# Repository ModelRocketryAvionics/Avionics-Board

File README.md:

# ModelRocketAvionicsPCB
'Cheap', Easy Avionics for Model Rockets!

Howdy! This is a repo for an avionics board designed for small scale model rockets. The goal of the project is to provide an easy to integrate system that provides telemetry data measurements. 

The main features are:
- 3 DOF Accelerometer (upto 24g)
- 3 DOF Gyroscope
- Barometric Pressure/Altitude sensor
- microSD Card data storage
- USB for charging, reprogramming and microSD card reading*
- Expansion header for future functionality called "Stages" (see below)

*Usb programming and microSD card reading probably won't be implemented initially.

Potential/Planned Stages/Expansion Boards:
- Radio link/communications (Provides real-time telemetry data over a short range wireless link)
- Relay/Switcher (Provides high-power switching for ignition of additional charges/engines, deploy parachutes, etc)
- Additional Sensors Expansions (Additional Sensors like GPS, etc)

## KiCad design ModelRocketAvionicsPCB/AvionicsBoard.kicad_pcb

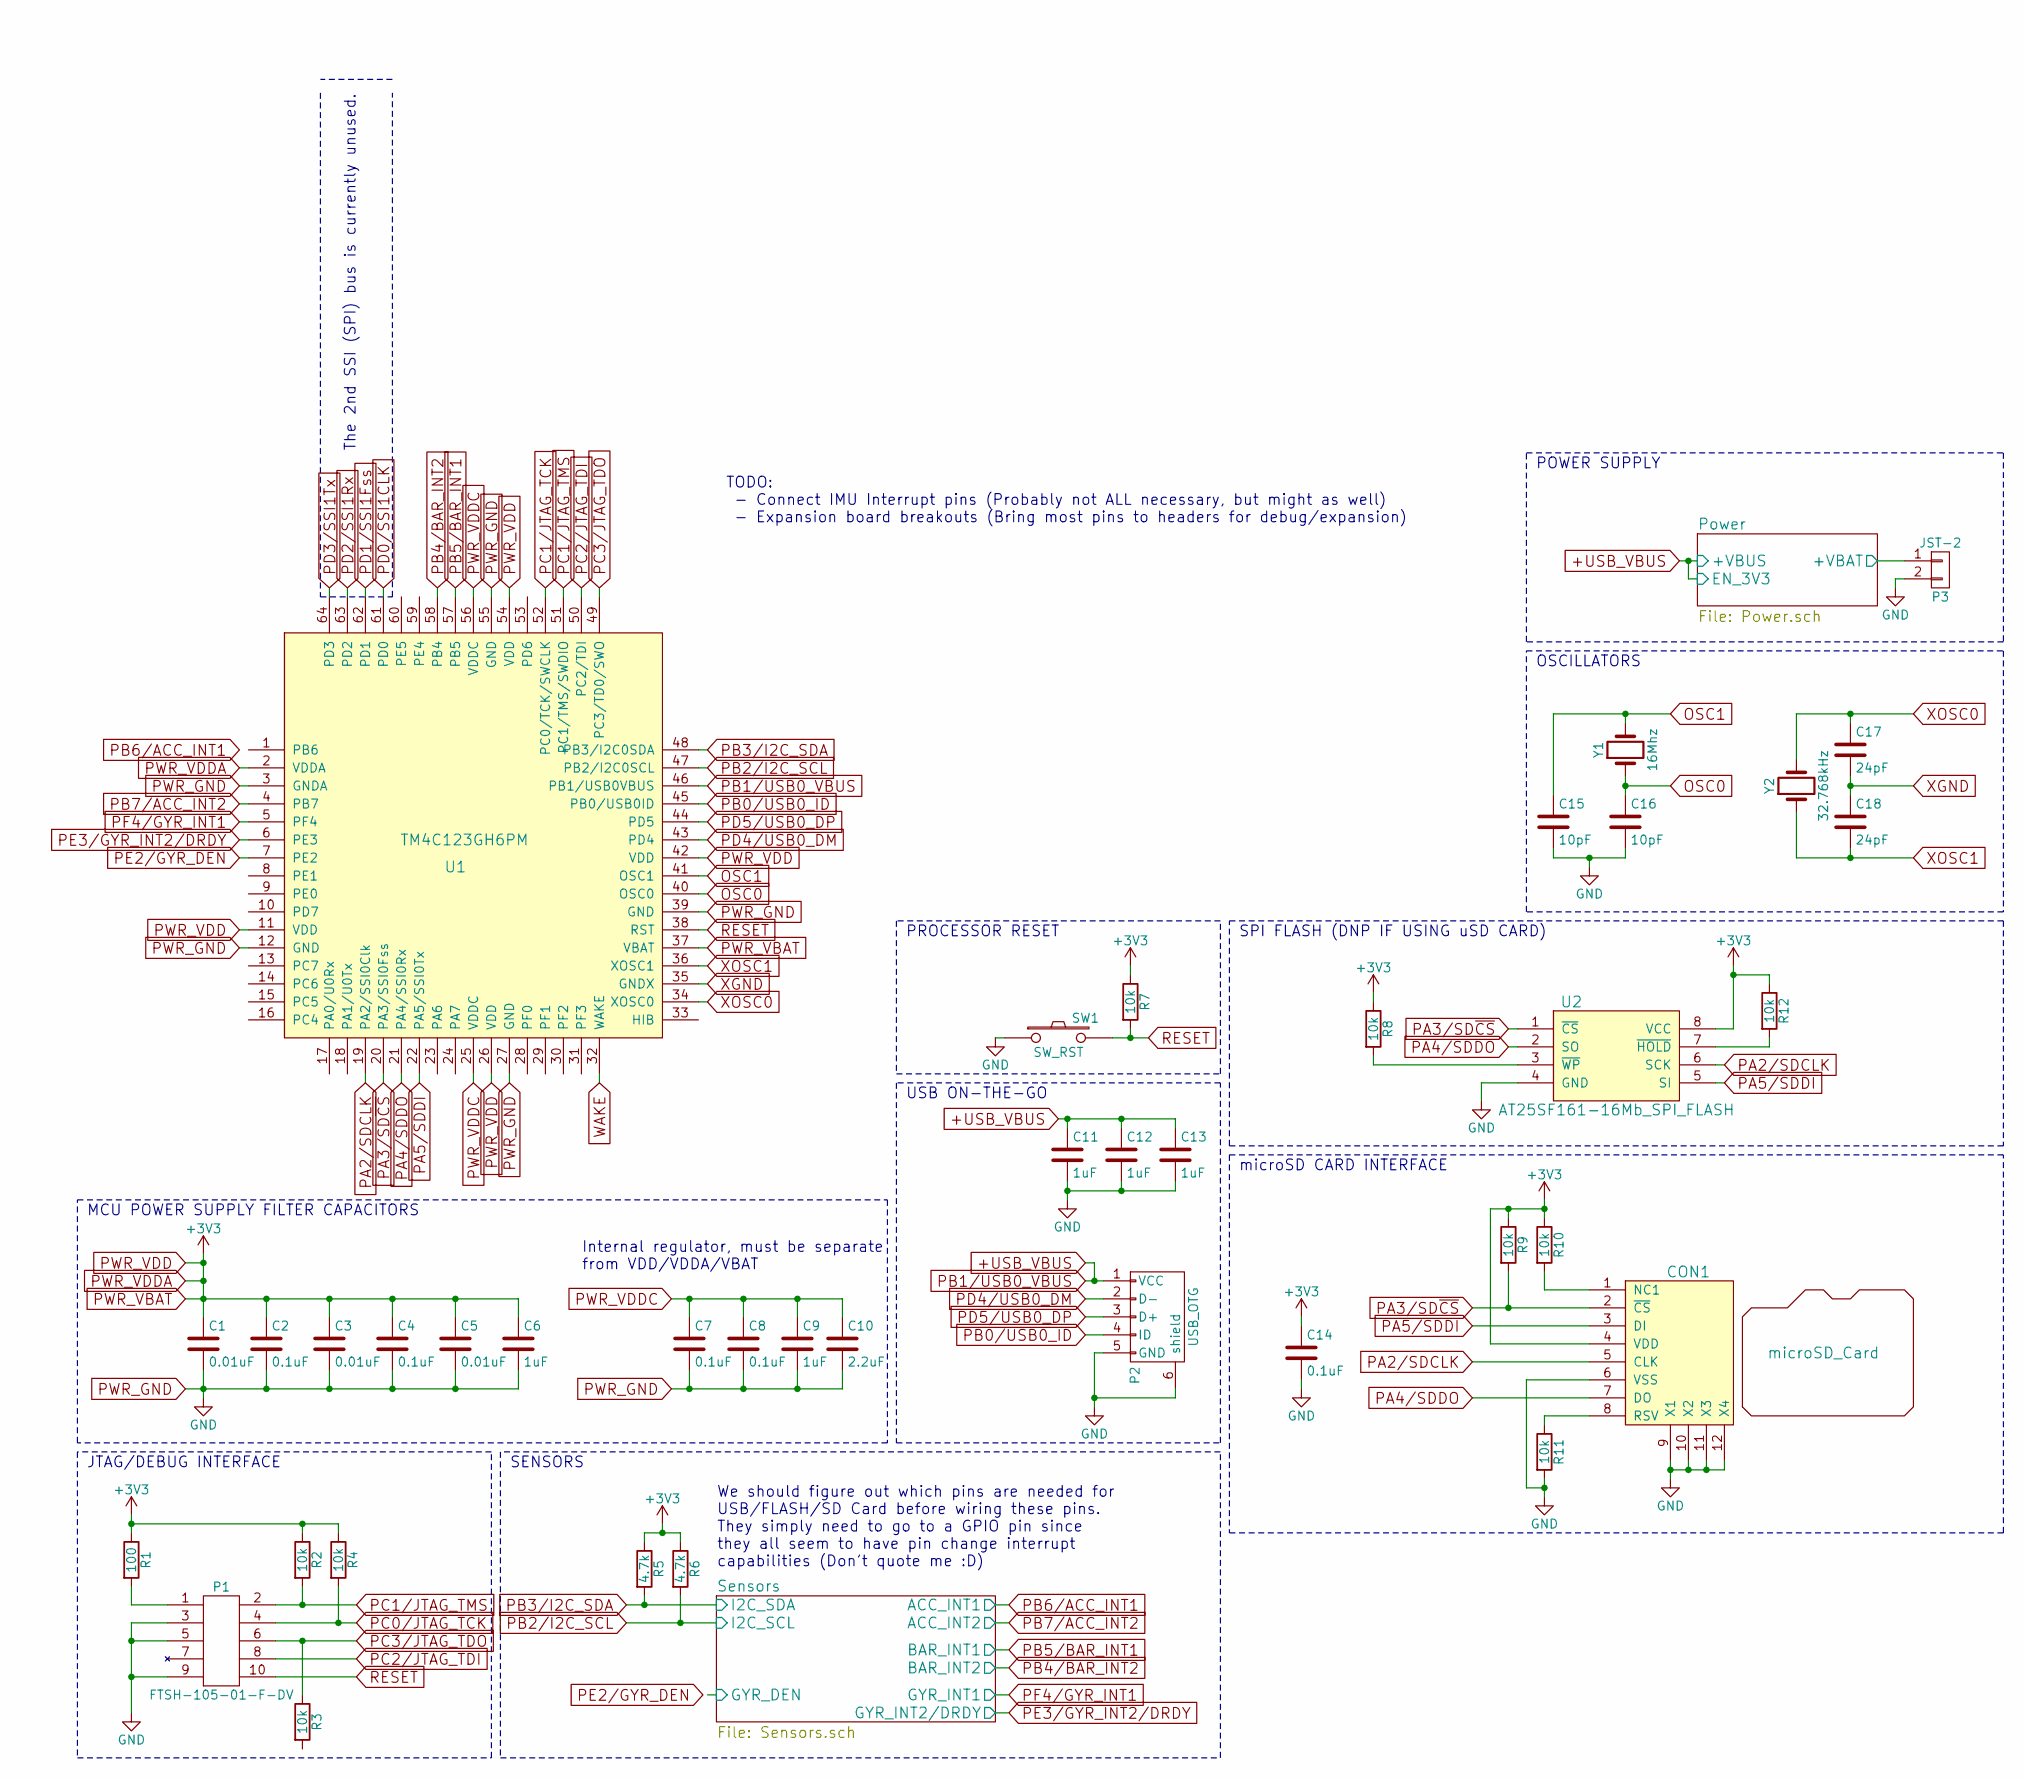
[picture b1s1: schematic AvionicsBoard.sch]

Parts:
C1, C3, C5: 0.01uF; C_0402; Digi-Key Part Number 478-7867-1-ND
C2, C4, C7, C8, C14: 0.1uF; C_0402; Digi-Key Part Number 587-4552-1-ND
C6, C9, C11, C12, C13: 1uF; C_0603; Digi-Key Part Number 490-1543-1-ND
C10: 2.2uF; C_0603; Digi-Key Part Number 490-3296-1-ND
C15, C16: 10pF; C_0402; Digi-Key Part Number 712-1252-1-ND
C17: 24pF; C_0402; Digi-Key Part Number 478-10149-1-ND
C18: 24pF; C_0402
CON1: microSD_Card; Micro_SD_WM11190CT; Digi-Key Part Number WM11190CT-ND
P1: FTSH-105-01-F-DV; FTSH-105-01-F-DV-K; Digi-Key Part Number SAM8796-ND
P2: USB_OTG; USB_Connector_ZX62-B-5PA; Digi-Key Part Number H125279CT-ND
P3: JST-2; JST_B2B-EH-A(LF)(SN); Digi-Key Part Number 455-1611-ND
R1: 100; R_0402; Digi-Key Part Number P100DECT-ND
R2, R3, R4, R7, R8, R9, R10, R11, R12: 10k; R_0402; Digi-Key Part Number 311-10.0KLRCT-ND
R5, R6: 4.7k; R_0402; Digi-Key Part Number P4.7KDCCT-ND
SW1: SW_RST; Push_Button_B3S-1000; Digi-Key Part Number SW415-ND
U1: TM4C123GH6PM; TM4C123GH6PMI; Digi-Key Part Number 296-46360-1-ND
U2: AT25SF161-16Mb_SPI_FLASH; Flash_Mem_AT25SF161-SSHD; Digi-Key Part Number 1265-1230-1-ND
Y1: 16Mhz; 16MHz_Clock; Manufacturer Part No NX5032GA-16.000000MHZ-LN-CD-1; Digi-Key Part Number 631-1150-1-ND
Y2: 32.768kHz; Crystal_32768Hz_Radial_Can; Digi-Key Part Number 535-9034-ND

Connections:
+USB_VBUS: C11.1, C12.1, C13.1, P2.1 (VCC), U1.46 (PB1/USB0VBUS); also elsewhere on the board
+VBAT: P3.1; also elsewhere on the board
ACC_CS: C1.1, C2.1, C3.1, C4.1, C5.1, C6.1, C14.1, CON1.4 (VDD), R1.1, R2.1, R4.1, R5.1, R6.1, R7.1, R8.1, R9.1, R10.1, R12.1, U1.2 (VDDA), U1.11 (VDD), U1.26 (VDD), U1.37 (VBAT), U1.42 (VDD), U1.54 (VDD), U2.8 (VCC); also elsewhere on the board
HIB: U1.33 (HIB); also elsewhere on the board
unnamed 10: CON1.1 (NC1), R10.2; also elsewhere on the board
unnamed 11: CON1.8 (RSV), R11.1; also elsewhere on the board
unnamed: P1.1 (3V3), R1.2
unnamed: R8.2, U2.3 (~WP)
unnamed: R12.2, U2.7 (~HOLD)
OSC0: C16.1, U1.40 (OSC0), Y1.1
OSC1: C15.1, U1.41 (OSC1), Y1.2
PA0/U0Rx: U1.17 (PA0/U0Rx); also elsewhere on the board
PA1/U0Tx: U1.18 (PA1/U0Tx); also elsewhere on the board
PA2/SDCLK: CON1.5 (CLK), U1.19 (PA2/SSI0Clk), U2.6 (SCK); also elsewhere on the board
PA3/SD~CS: CON1.2 (~CS), R9.2, U1.20 (PA3/SSI0Fss), U2.1 (~CS); also elsewhere on the board
PA4/SDDO: CON1.7 (DO), U1.21 (PA4/SSI0Rx), U2.2 (SO); also elsewhere on the board
PA5/SDDI: CON1.3 (DI), U1.22 (PA5/SSI0Tx), U2.5 (SI); also elsewhere on the board
PA6: U1.23 (PA6); also elsewhere on the board
PA7: U1.24 (PA7); also elsewhere on the board
PB0/USB0_ID: P2.4 (ID), U1.45 (PB0/USB0ID)
PB2/I2C_SCL: R6.2, U1.47 (PB2/I2C0SCL); also elsewhere on the board
PB3/I2C_SDA: R5.2, U1.48 (PB3/I2C0SDA); also elsewhere on the board
PB4: U1.58 (PB4); also elsewhere on the board
PB5: U1.57 (PB5); also elsewhere on the board
PB6/GYR_INT2/DRDY: U1.1 (PB6); also elsewhere on the board
PB7/GYR_INT1: U1.4 (PB7); also elsewhere on the board
PC1/JTAG_TMS: P1.2 (JTAG_TMS), R2.2, U1.51 (PC1/TMS/SWDIO)
PC2/JTAG_TDI: P1.8 (JTAG_TDO), U1.50 (PC2/TDI)
PC3/JTAG_TDO: P1.6 (JTAG_TDO), R3.1, U1.49 (PC3/TD0/SWO)
PC4: U1.16 (PC4); also elsewhere on the board
PC5: U1.15 (PC5); also elsewhere on the board
PC6: U1.14 (PC6); also elsewhere on the board
PC7: U1.13 (PC7); also elsewhere on the board
PD0/SSI1CLK: U1.61 (PD0); also elsewhere on the board
PD1/SSI1Fss: U1.62 (PD1); also elsewhere on the board
PD2/SSI1Rx: U1.63 (PD2); also elsewhere on the board
PD3/SSI1Tx: U1.64 (PD3); also elsewhere on the board
PD6: U1.53 (PD6); also elsewhere on the board
PD7: U1.10 (PD7); also elsewhere on the board
PE0: U1.9 (PE0); also elsewhere on the board
PE1/IND_LED: U1.8 (PE1); also elsewhere on the board
PE2/ACC_INT2: U1.7 (PE2); also elsewhere on the board
PE3/ACC_INT1: U1.6 (PE3); also elsewhere on the board
PE4: U1.59 (PE4); also elsewhere on the board
PE5: U1.60 (PE5); also elsewhere on the board
PF0: U1.28 (PF0)
PF1: U1.29 (PF1)
PF2/BAR_INT1: U1.30 (PF2); also elsewhere on the board
PF3/BAR_INT2: U1.31 (PF3); also elsewhere on the board
PF4/GYR_DEN: U1.5 (PF4); also elsewhere on the board
PWR_GND: C1.2, C2.2, C3.2, C4.2, C5.2, C6.2, C7.2, C8.2, C9.2, C10.2, C11.2, C12.2, C13.2, C14.2, C15.2, C16.2, CON1.6 (VSS), CON1.9 (X1), CON1.10 (X2), CON1.11 (X3), CON1.12 (X4), P1.3 (GND), P1.5 (GND), P1.9 (GND), P2.5 (GND), P2.6 (shield), P3.2, R3.2, R11.2, SW1.1, U1.3 (GNDA), U1.12 (GND), U1.27 (GND), U1.39 (GND), U1.55 (GND), U2.4 (GND); also elsewhere on the board
PWR_VDDC: C7.1, C8.1, C9.1, C10.1, U1.25 (VDDC), U1.56 (VDDC)
RESET: P1.10 (RST_N), R7.2, SW1.2, U1.38 (RST); also elsewhere on the board
USB0_D+: P2.3 (D+), U1.44 (PD5)
USB0_D-: P2.2 (D-), U1.43 (PD4)
WAKE: U1.32 (WAKE); also elsewhere on the board
XGND: C17.2, C18.1, U1.35 (GNDX)
XOSC0: C17.1, U1.34 (XOSC0), Y2.2
XOSC1: C18.2, U1.36 (XOSC1), Y2.1

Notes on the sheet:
We should figure out which pins are needed for USB/FLASH/SD Card before wiring these pins. They simply need to go to a GPIO pin since they all seem to have pin change interrupt capabilities (Don't quote me :D)
JTAG/DEBUG INTERFACE
SENSORS
MCU POWER SUPPLY FILTER CAPACITORS
Internal regulator, must be separate from VDD/VDDA/VBAT
microSD CARD INTERFACE
SPI FLASH (DNP IF USING uSD CARD)
USB ON-THE-GO
TODO: - Connect IMU Interrupt pins (Probably not ALL necessary, but might as well) - Expansion board breakouts (Bring most pins to headers for debug/expansion)
The 2nd SSI (SPI) bus is currently unused.
OSCILLATORS
PROCESSOR RESET
POWER SUPPLY

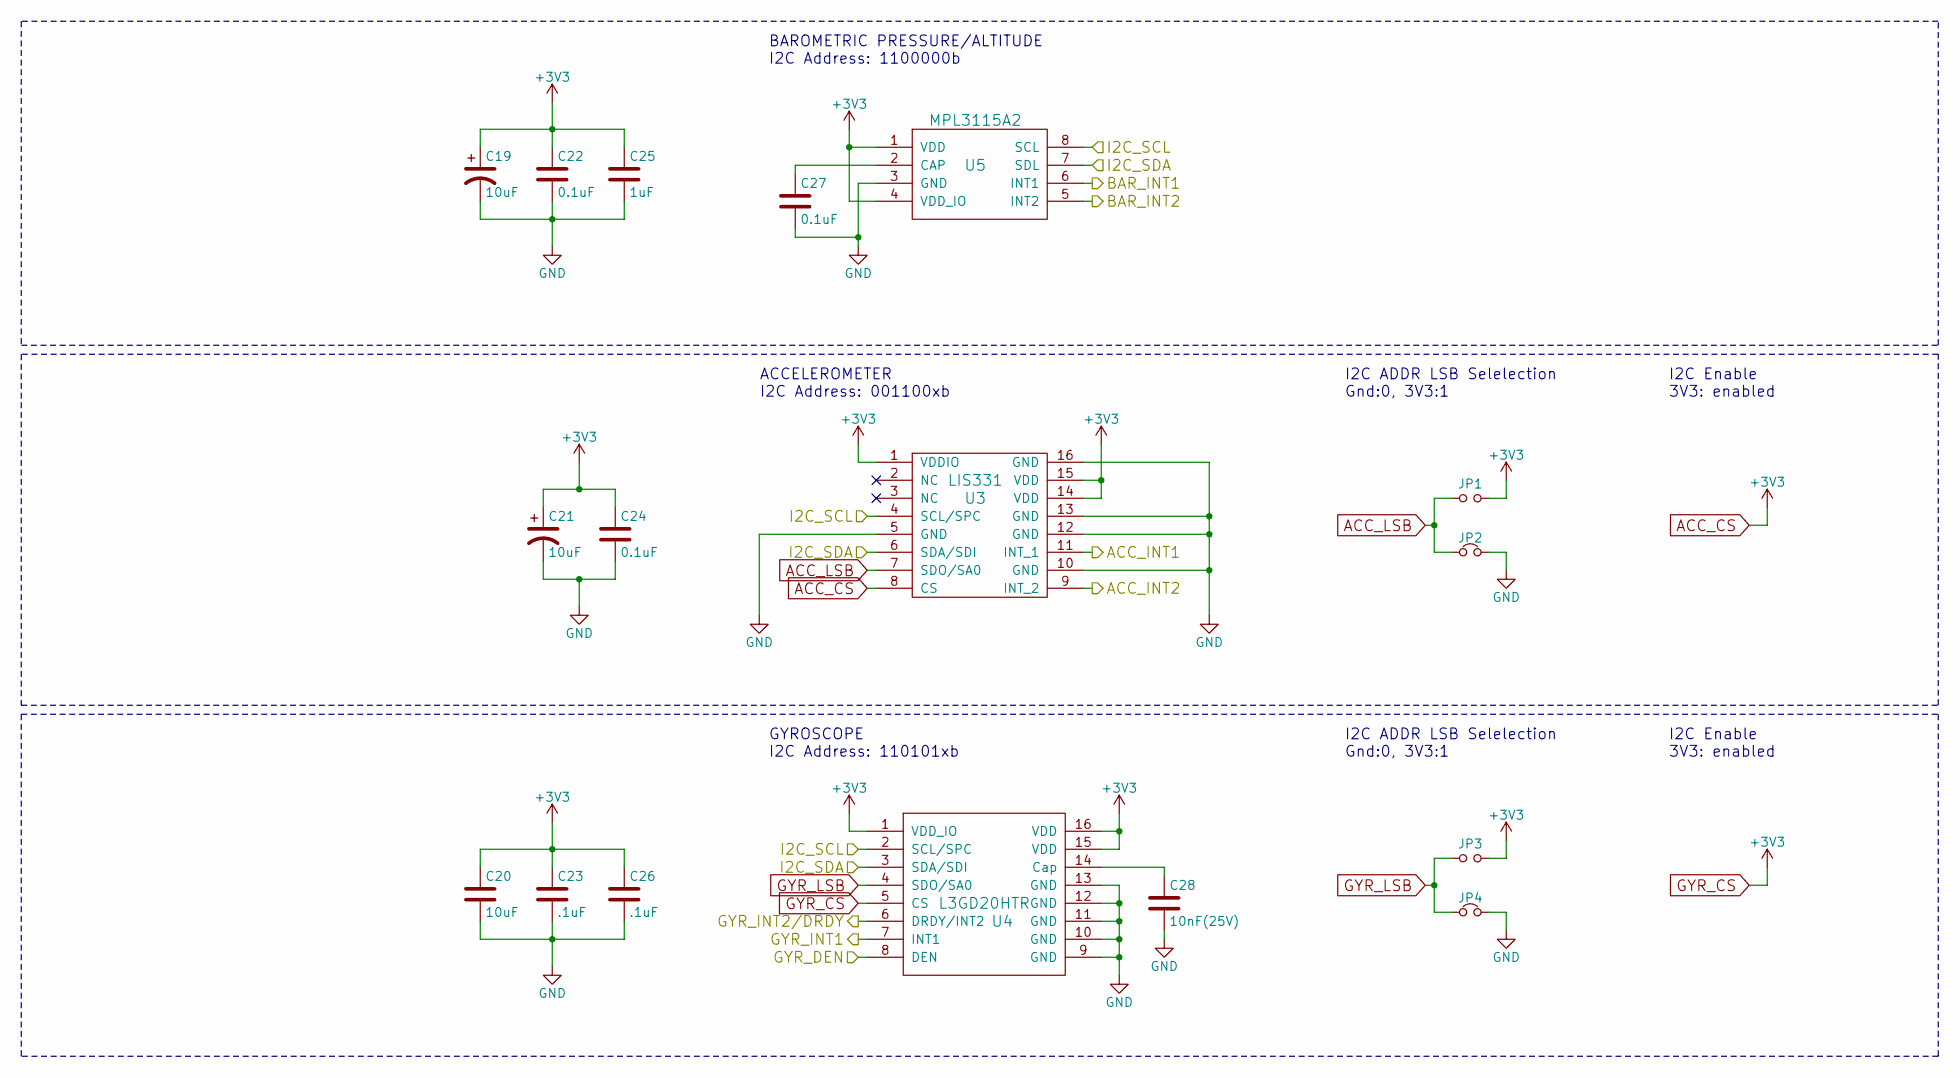
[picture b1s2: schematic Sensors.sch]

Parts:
C19, C21: 10uF; C_1206; Digi-Key Part Number 478-10756-1-ND
C20: 10uF; C_0603; Digi-Key Part Number 1276-1871-1-ND
C22, C24, C27: 0.1uF; C_0402; Digi-Key Part Number 587-4552-1-ND
C23, C26: .1uF; C_0402; Digi-Key Part Number 587-4552-1-ND
C25: 1uF; C_0603; Digi-Key Part Number 490-1543-1-ND
C28: 10nF(25V); C_0402; Digi-Key Part Number 478-7867-1-ND
JP1, JP3: Jumper_NO_Small; NO_Jumper
JP2, JP4: Jumper_NC_Small; NC_Jumper
U3: LIS331; LIS331HH; Digi-Key Part Number 497-10134-ND
U4: L3GD20HTR; Gyro_L3GD20HTR; Digi-Key Part Number 497-13931-1-ND
U5: MPL3115A2; Digi-Key Part Number MPL3115A2-ND

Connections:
ACC_CS: C19.1, C20.1, C21.1, C22.1, C23.1, C24.1, C25.1, C26.1, JP1.2, JP3.2, U3.1 (VDDIO), U3.8 (CS), U3.14 (VDD), U3.15 (VDD), U4.1 (VDD_IO), U4.5 (CS), U4.15 (VDD), U4.16 (VDD), U5.1 (VDD), U5.4 (VDD_IO); also elsewhere on the board
ACC_LSB: JP1.1, JP2.1, U3.7 (SDO/SA0)
GYR_LSB: JP3.1, JP4.1, U4.4 (SDO/SA0)
unnamed: C27.1, U5.2 (CAP)
unnamed: C28.1, U4.14 (Cap)
PB2/I2C_SCL: U3.4 (SCL/SPC), U4.2 (SCL/SPC), U5.8 (SCL); also elsewhere on the board
PB3/I2C_SDA: U3.6 (SDA/SDI), U4.3 (SDA/SDI), U5.7 (SDL); also elsewhere on the board
PB6/GYR_INT2/DRDY: U4.6 (DRDY/INT2); also elsewhere on the board
PB7/GYR_INT1: U4.7 (INT1); also elsewhere on the board
PE2/ACC_INT2: U3.9 (INT_2); also elsewhere on the board
PE3/ACC_INT1: U3.11 (INT_1); also elsewhere on the board
PF2/BAR_INT1: U5.6 (INT1); also elsewhere on the board
PF3/BAR_INT2: U5.5 (INT2); also elsewhere on the board
PF4/GYR_DEN: U4.8 (DEN); also elsewhere on the board
PWR_GND: C19.2, C20.2, C21.2, C22.2, C23.2, C24.2, C25.2, C26.2, C27.2, C28.2, JP2.2, JP4.2, U3.5 (GND), U3.10 (GND), U3.12 (GND), U3.13 (GND), U3.16 (GND), U4.9 (GND), U4.10 (GND), U4.11 (GND), U4.12 (GND), U4.13 (GND), U5.3 (GND); also elsewhere on the board

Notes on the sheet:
I2C ADDR LSB Selelection Gnd:0, 3V3:1
I2C Enable 3V3: enabled
ACCELEROMETER I2C Address: 001100xb
BAROMETRIC PRESSURE/ALTITUDE I2C Address: 1100000b
GYROSCOPE I2C Address: 110101xb

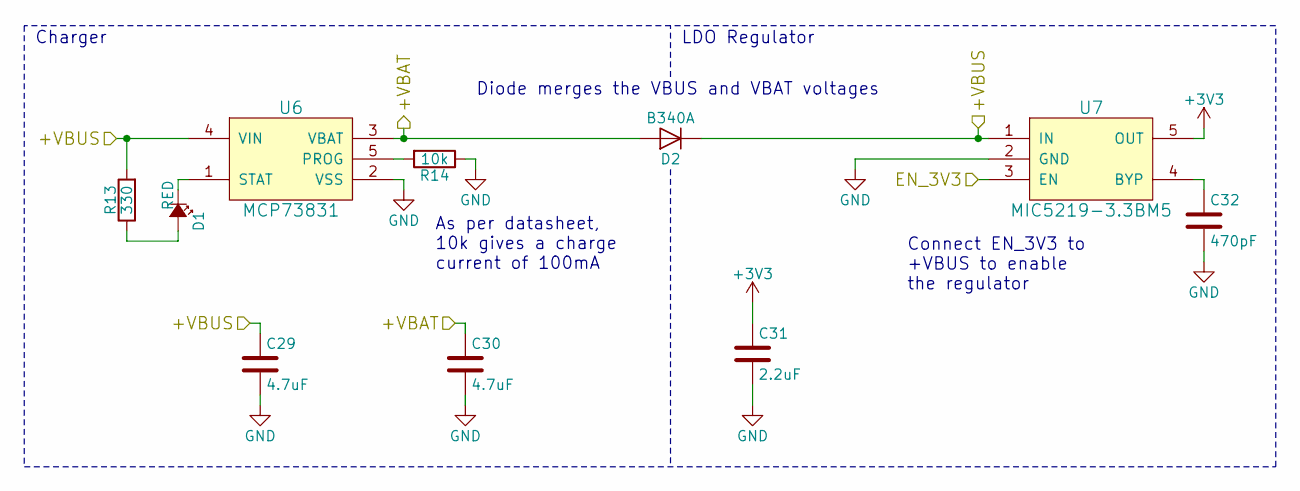
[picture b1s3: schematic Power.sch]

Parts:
C29, C30: 4.7uF; C_0603; Rated Voltage 16V; Digi-Key Part Number 445-7478-1-ND
C31: 2.2uF; C_0603; Digi-Key Part Number 490-3296-1-ND
C32: 470pF; C_0402; Digi-Key Part Number 490-1300-1-ND
D1: RED; R_0603; Digi-Key Part Number 160-1447-1-ND
D2: B340A; Digi-Key Part Number B340A-FDICT-ND
R13: 330; R_0402; Digi-Key Part Number RR05P330DCT-ND
R14: 10k; R_0402; Digi-Key Part Number 311-10.0KLRCT-ND
U6: MCP73831; MCP73831T-2ACI&slash_OT; Digi-Key Part Number MCP73831T-2ACI/OTCT-ND
U7: MIC5219-3.3BM5; MIC5219-3.3YM5-TR; Digi-Key Part Number 576-1281-1-ND

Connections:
+USB_VBUS: C29.1, D2.1 (K), R13.2, U6.4 (VIN), U7.1 (IN), U7.3 (EN); also elsewhere on the board
+VBAT_ON: C30.1, D2.2 (A), U6.3 (VBAT); also elsewhere on the board
ACC_CS: C31.1, U7.5 (OUT); also elsewhere on the board
unnamed: C32.1, U7.4 (BYP)
unnamed: D1.1 (K), U6.1 (STAT)
unnamed: D1.2 (A), R13.1
unnamed: R14.2, U6.5 (PROG)
PWR_GND: C29.2, C30.2, C31.2, C32.2, R14.1, U6.2 (VSS), U7.2 (GND); also elsewhere on the board

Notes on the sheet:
Diode merges the VBUS and VBAT voltages
Charger
LDO Regulator
As per datasheet, 10k gives a charge current of 100mA
Connect EN_3V3 to +VBUS to enable the regulator

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
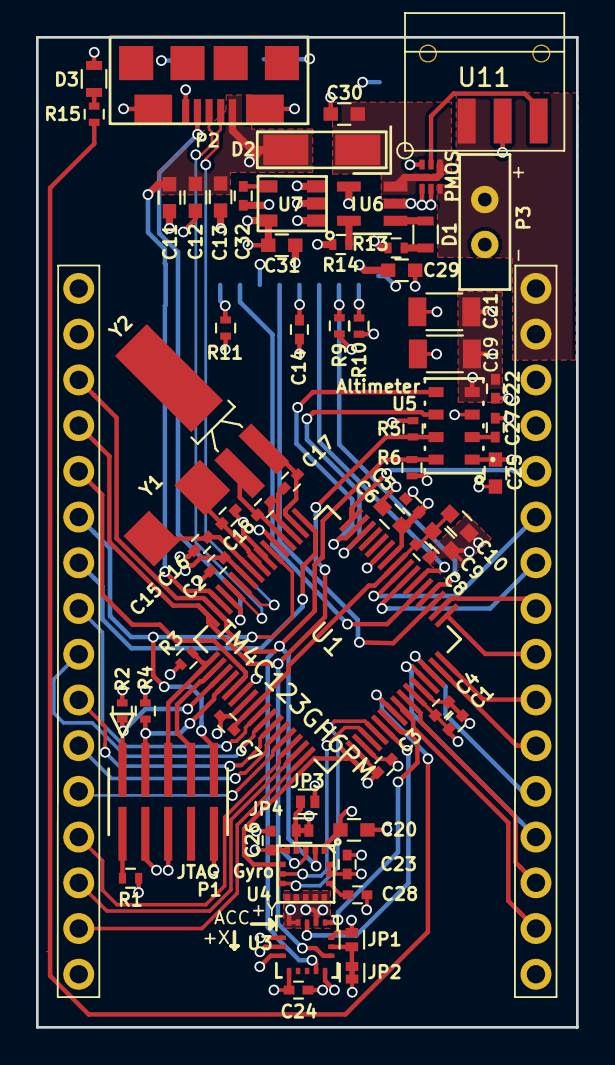
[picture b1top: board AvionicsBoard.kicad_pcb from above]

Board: 4 copper layers, 30.0 x 55.0 mm, 67 parts (1 on the bottom side), 67 nets.

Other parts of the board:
D3: Led_Small; R_0603
R15: 100; R_0402
U8, U9: CONNHeaderFemale16; 16x1_Female_Header
U10: DMG1029SV-7; SOT563
U11: CSS-1210TB
microSD_Card: microSD_Card; Micro_SD_WM11190CT

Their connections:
+VBAT: U8.1, U8.2, U10.6, U11.1; also elsewhere on the board
+VBAT_ON: U10.1; also elsewhere on the board
ACC_CS: U8.3, U8.4, U9.16, microSD_Card.4; also elsewhere on the board
HIB: U9.7; also elsewhere on the board
unnamed 10: microSD_Card.1; also elsewhere on the board
unnamed 11: microSD_Card.8; also elsewhere on the board
unnamed: D3.2, R15.1
PA0/U0Rx: U8.9; also elsewhere on the board
PA1/U0Tx: U8.8; also elsewhere on the board
PA2/SDCLK: microSD_Card.5; also elsewhere on the board
PA3/SD~CS: microSD_Card.2; also elsewhere on the board
PA4/SDDO: microSD_Card.7; also elsewhere on the board
PA5/SDDI: microSD_Card.3; also elsewhere on the board
PA6: U8.7; also elsewhere on the board
PA7: U8.6; also elsewhere on the board
PB2/I2C_SCL: U9.3; also elsewhere on the board
PB3/I2C_SDA: U9.4; also elsewhere on the board
PB4: U9.9; also elsewhere on the board
PB5: U9.8; also elsewhere on the board
PC4: U8.10; also elsewhere on the board
PC5: U8.11; also elsewhere on the board
PC6: U8.12; also elsewhere on the board
PC7: U8.13; also elsewhere on the board
PD0/SSI1CLK: U9.12; also elsewhere on the board
PD1/SSI1Fss: U9.13; also elsewhere on the board
PD2/SSI1Rx: U9.14; also elsewhere on the board
PD3/SSI1Tx: U9.15; also elsewhere on the board
PD6: U9.5; also elsewhere on the board
PD7: U8.14; also elsewhere on the board
PE0: U8.15; also elsewhere on the board
PE1/IND_LED: R15.2; also elsewhere on the board
PE4: U9.10; also elsewhere on the board
PE5: U9.11; also elsewhere on the board
PWR_GND: D3.1, U8.16, U9.1, U9.2, U10.3, U10.4, U10.5, U11.2, microSD_Card.6, microSD_Card.9, microSD_Card.10, microSD_Card.11, microSD_Card.12; also elsewhere on the board
PWR_SWITCH: U10.2, U11.3
RESET: U9.6; also elsewhere on the board
WAKE: U8.5; also elsewhere on the board

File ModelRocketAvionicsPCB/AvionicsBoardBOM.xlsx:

Avionics Board BOM
Reference Part Numbers | Reference Name | Digikey Part Number | Quantitity
U1 | TM4C123GH6PM | 296-46360-1-ND | 1
R1, R15 | 100 Ohm 402 | P100DECT-ND | 2
P1 | FTSH-105-01-F-DV | SAM8796-ND | 1
R2, R3, R4, R9, R10, R11, R14 | 10k Ohm 402 | ‎CR0402-FX-1002GLF‎ | 7
C1, C3, C5 | 0.01uF 402 | 1276-1494-1-ND | 3
C2, C4, C7, C8, C14, C22, C23, C24, C26, C27 | 0.1uF 402 | 490-6322-1-ND | 10
C6, C9, C11, C12, C13, C25 | 1uF 603 | 1276-1102-1-ND | 6
C10, C31 | 2.2uF 603 | 490-3296-1-ND | 1
R5, R6 | 4.7k Ohm 402 | P4.7KDCCT-ND | 2
C19, C21 | 10uF 1206 Pol | 478-10756-1-ND | 2
U5 | MPL3115A2 | MPL3115A2-ND | 1
U3 | LIS331 | 497-10134-ND | 1
C20 | 10uF 603 | 1276-1871-1-ND | 1
C28 | 10nF 402 | 445-5584-1-ND | 1
U4 | L3GD2-HTR | 497-13931-1-ND | 1
P2 | USB_Connector_ZX62-B-5PA | H125279CT-ND | 1
CON1 | microSD_Card | WM11190CT-ND | 1
C17, C18 | 24pF 402 | 1276-1670-1-ND | 2
C15, C16 | 10pF 402 | ‎GJM1555C1H100GB01D‎ | 2
Y1 | 16MHz | 631-1150-1-ND | 1
Y2 | 32.768kHz | 535-9034-ND | 1
U8, U9 | 16pin Female Headers | S7014-ND | 2
D3 | Geend Small LED 603 | 160-1435-1-ND | 1
P3 | JST-2 | 455-1611-ND | 1
U10 | DMG1029SV-7 | DMP2004VKDICT-ND | 1
U11 | CSS-1210TB | 563-1091-1-ND | 1
C29, C30 | 4.7uF 603 | 445-7478-1-ND | 2
C32 | 470pF 402 | 490-1300-1-ND | 1
R13 | 330 Ohm 402 | RR05P330DCT-ND | 1
D1 | Small Red LED 603 | 160-1447-1-ND | 1
D2 | B340A | B340A-FDICT-ND | 1
U6 | MCP73831 | MCP73831T-2ACI/OTCT-ND | 1
U7 | MIC5219-3.3BM5 | 576-1281-1-ND | 1
Total Number of Parts per Board |  |  | 62

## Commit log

2018-03-25 :boom::camel: Added .gitattributes & .gitignore files
2018-04-28 Schematic Started
2018-04-30 Compiled sensors on another Sheet, added uSD card/flash chip, jtag interface, power supply filter caps and started to add USB OTG
2018-05-01 Added oscillators and reset button/circuit
2018-05-01 Critical features/components of avionics board schematic are complete (needs review). Still need to figure out a logical expansion header pinout and place the headers.
2018-05-01 Added IMU interrupt pin wiring to TODO and created a basic PDF of the current schematic
2018-05-01 Annotated components and added 'Digi-Key Part Numbers' for most of the non-passives
2018-05-28 Added file structure for the firmware integration
2018-05-28 Created Readme
2018-05-28 Added pin allocation excel sheet for planning/documentation
2018-05-28 Added User switches and LED to the pcb schematic
2018-05-30 oh no
2018-05-30 Added footprint for RTC crystal
2018-05-31 Added Footprints for non-passives
2018-06-06 Footprints Completed
    Except Jumper Footprints
2018-06-06 Changed polarized caps to use 1206 and digikey part number: 478-10756-1-ND
2018-06-07 Began Preliminary Layout
2018-06-16 Completed Preliminary Layout
2018-07-13 Added 16 pin Female Headers
2018-07-14 Partially Complete Updated Avionics Layout
    Final Pinout and Silk Screen still needs to be completed.
2018-07-14 CDR Ready Board
2018-07-15 Updated Sch
2018-07-15 Schematic Check Complete
2018-07-15 Pushed
2018-07-15 DRC Issues Solved
2018-07-15 CDR Complete
2018-07-16 Created a new PDF file of the schematic for reference
2018-07-17 Final Board REV 1a - Gerber Files
2018-07-19 Updated for certainity
2018-07-26 First real commit! Started writing the Scheduler (sch.c/.h), currently untested. See TIVA C Worksbook Lab2 for IDE setup instructions.
2018-07-27 Started doing SPI, CC2500 and Serial support, still untested

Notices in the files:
parts and their libraries:
Copyright 2016 Accelerated Designs. All rights reserved.
